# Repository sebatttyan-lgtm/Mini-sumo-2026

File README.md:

# MARK 38(mini sumo)

## DESCRIPCIÓN
El proyecto es un robot mini sumo diseñado por nosotros, con un tamaño y peso correspondiente a las [reglas de la LNR (Liga Nacional de Robótica)](https://sistema.lnr-argentina.com.ar/reglamentos/Sumo). este tiene la capacidad de detectar al contrincante para ir y atacar al otro mini sumo con el que este compitiendo para dejarlo fuera del dojo.

## ADMINISTRADORES DEL PROYECTO
1. **Thiago Lopez.** Diseño 3D y montaje de componentes en placa.
2. **Enzo Zapata.** Diseño de PCB, esquemático y montaje de componentes en placa. 
3. **Sebastián Pérez.** Programación, diseño esquemático y PCB y montaje de componentes en placa. 

## OBJETIVO
Nuestra meta con este proyecto es poder participar en la [LNR(Liga Nacional de Robótica)](https://lnr-argentina.com.ar/) y quedar en un puesto alto a la hora de terminar la competencia.Además, queremos lograr también la programación de mini sumo RC para poder competir entre amigos. 

## ESPECIFICACIONES TÉCNICAS
#### Tamaño del mini sumo: 10cm x 10cm x 8cm
#### Alimentación de operación: 11.1v 450mAh
#### Material empleado en la carrocería: PLA
#### Tipos de sensores empleados: Infrarrojo
#### Fuerza de torque:30Nm (Newton metros)

## COMPONENTES
### - SENSORES DE OBSTÁCULOS
#### [VL53L0X](https://components101.com/sensors/vl53l0x-lidar-distance-sensor) *(x5)*
### - SENSORES DE PISO
#### [QRE1113](https://www.alldatasheet.es/datasheet-pdf/view/54347/FAIRCHILD/QRE1113.html) *(x2)*
### - MOTORES
#### [MICROMOTORES N30 500rpm](https://www.aslongdcmotor.com/photo/aslongdcmotor/document/26865/JGA12-N30.pdf) *(x2)*
### - MICROCONTROLADOR 
#### [ESP32 C3 super mini](www.google.com/search?q=esp32+c3+super+mini&oq=esp32+c3+super+mini&gs_lcrp=EgZjaHJvbWUyBggAEEUYOdIBCDg1NzBqMGo3qAIAsAIA&sourceid=chrome&ie=UTF-8) *(x1)* 
### - DRIVER DE MOTOR (puente H)
#### [TA6586](https://www.alldatasheet.com/datasheet-pdf/pdf/1761575/RZ-MIC/TA6586.html) *(x2)*
### - BATERIA
#### [Tattu 3S 450mAh 11.1V 75C XT30](https://www.hobbymotors.com.ar/store/index.php?route=product/product&product_id=1127) *(x1)*
> (estos componentes son a grandes rasgos y no se han colocado todos los componentes, en el archivo "lista de componentes se encontrarán todos los materiales utilizados durante la produccion").

## DISEÑO DE LA PLACA

<div align="center">

## DISEÑO ESQUEMÁMITCO

<div align="center">

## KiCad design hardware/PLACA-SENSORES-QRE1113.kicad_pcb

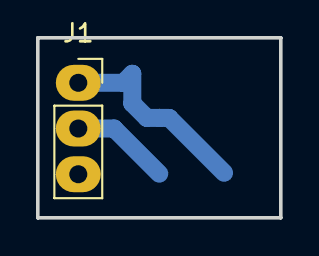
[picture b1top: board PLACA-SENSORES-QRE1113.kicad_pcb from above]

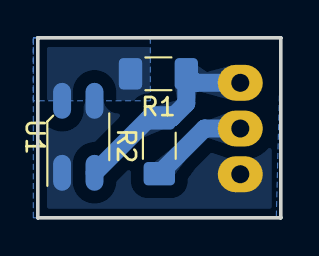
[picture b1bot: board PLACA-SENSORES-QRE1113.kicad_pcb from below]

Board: 2 copper layers, 13.5 x 10.0 mm, 4 parts (3 on the bottom side), 4 nets.

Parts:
J1: Conn_01x03; PinSocket_1x03_P2.54mm_Vertical
R1: 100; R_1206_3216Metric_Pad1.30x1.75mm_HandSolder
R2: 220; R_1206_3216Metric_Pad1.30x1.75mm_HandSolder
U1: QRE1113; OnSemi_CASE100AQ

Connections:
GND: J1.3, U1.2 (K), U1.4
unnamed: J1.2, R2.1
unnamed: R1.2, U1.1 (A)
VCC: J1.1, R1.1, R2.2, U1.3

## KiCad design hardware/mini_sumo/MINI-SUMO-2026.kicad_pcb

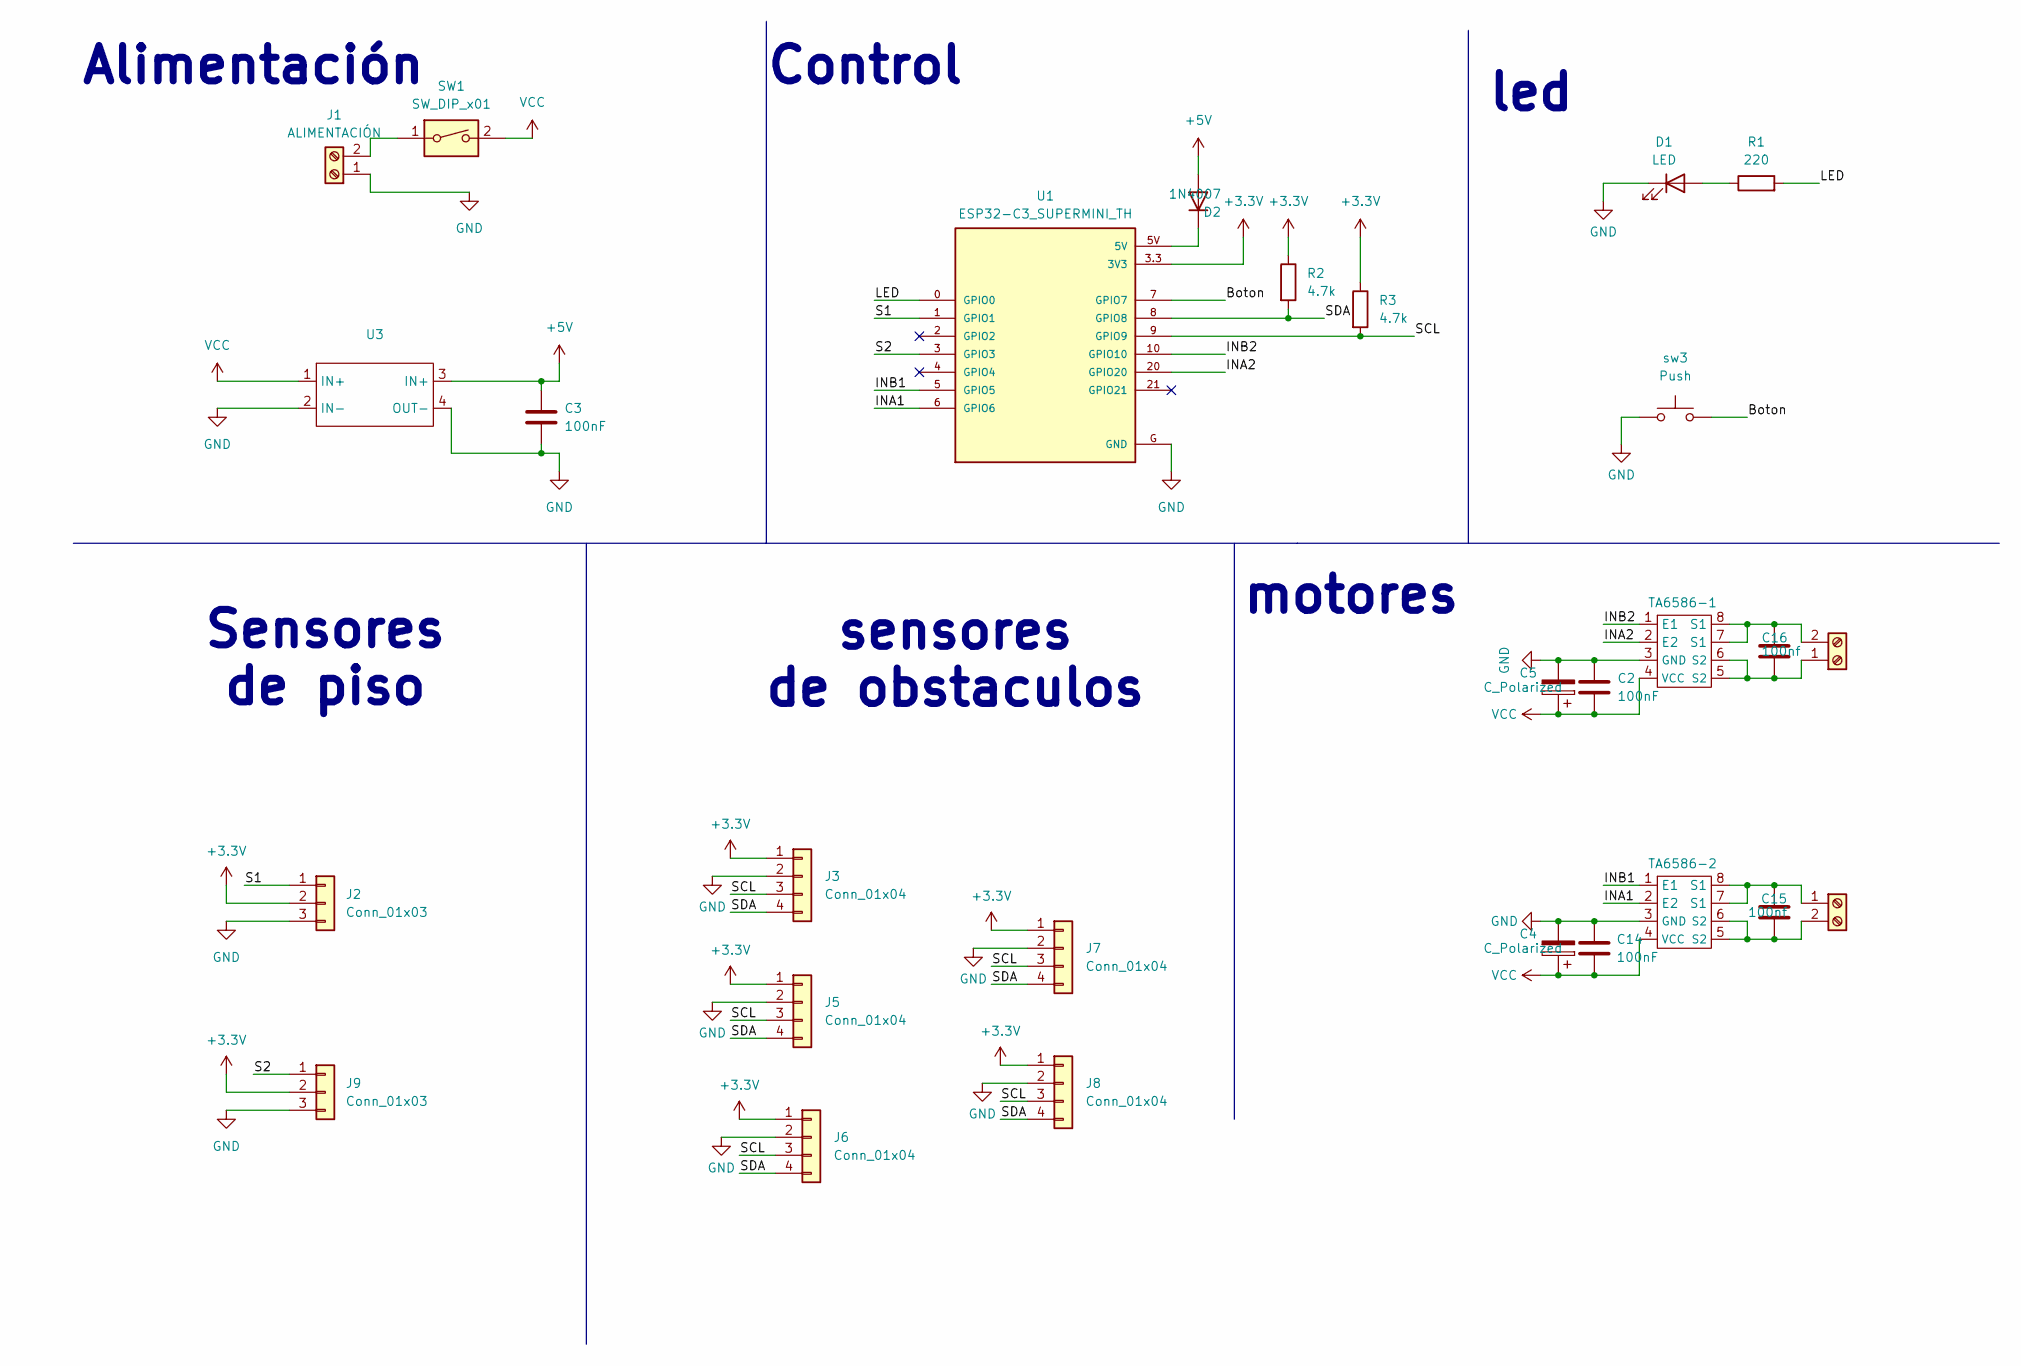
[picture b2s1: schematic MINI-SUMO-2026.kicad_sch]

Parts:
C2, C3, C14: 100nF; C_0805_2012Metric_Pad1.18x1.45mm_HandSolder
C4, C5: C_Polarized; C_Radial_D8.0mm_H11.5mm_P3.50mm
C15, C16: 100nf; C_0805_2012Metric_Pad1.18x1.45mm_HandSolder
D1: LED; PinHeader_1x02_P2.54mm_Vertical
D2: 1N4007; D_SMA_Handsoldering
J1: ALIMENTACIÓN; AMASS_XT30U-F_1x02_P5.0mm_Vertical
J2, J9: Conn_01x03; PinHeader_1x03_P2.54mm_Vertical
J3, J5, J6, J7, J8: Conn_01x04; PinHeader_1x04_P2.54mm_Vertical
M1: M1; JST_XH_S2B-XH-A-1_1x02_P2.50mm_Horizontal
M2: M2; JST_XH_S2B-XH-A-1_1x02_P2.50mm_Horizontal
R1: 220; R_0805_2012Metric_Pad1.20x1.40mm_HandSolder
R2, R3: 4.7k; R_0805_2012Metric_Pad1.20x1.40mm_HandSolder
SW1: SW_DIP_x01; PinHeader_1x02_P2.54mm_Vertical
TA6586-1, TA6586-2: DIP-8_W7.62mm
U1: ESP32-C3_SUPERMINI_TH; MODULE_ESP32-C3_SUPERMINI
U3: Mini360
sw3: Push; SW_PUSH_6mm_H4.3mm

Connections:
+3.3V: J2.2, J3.1, J5.1, J6.1, J7.1, J8.1, J9.2, R2.1, R3.1, U1.3.3 (3V3)
+5V: C3.1, D2.2 (A), U3.3 (IN+)
/Boton: U1.7 (GPIO7), sw3.2
/INA1: TA6586-2.2 (E2), U1.6 (GPIO6)
/INA2: TA6586-1.2 (E2), U1.20 (GPIO20)
/INB1: TA6586-2.1 (E1), U1.5 (GPIO5)
/INB2: TA6586-1.1 (E1), U1.10 (GPIO10)
/LED: R1.2, U1.0 (GPIO0)
/S1: J2.1, U1.1 (GPIO1)
/S2: J9.1, U1.3 (GPIO3)
/SCL: J3.3, J5.3, J6.3, J7.3, J8.3, R3.2, U1.9 (GPIO9)
/SDA: J3.4, J5.4, J6.4, J7.4, J8.4, R2.2, U1.8 (GPIO8)
GND: C2.1, C3.2, C4.2, C5.2, C14.1, D1.1 (K), J1.1, J2.3, J3.2, J5.2, J6.2, J7.2, J8.2, J9.3, TA6586-1.3 (GND), TA6586-2.3 (GND), U1.G (GND), U3.2 (IN-), U3.4 (OUT-), sw3.1
unnamed: D1.2 (A), R1.1
unnamed: D2.1 (K), U1.5V
unnamed: J1.2, SW1.1
unnamed: C16.2, M1.1, TA6586-1.5 (S2), TA6586-1.6 (S2)
unnamed: C16.1, M1.2, TA6586-1.7 (S1), TA6586-1.8 (S1)
unnamed: C15.1, M2.1, TA6586-2.7 (S1), TA6586-2.8 (S1)
unnamed: C15.2, M2.2, TA6586-2.5 (S2), TA6586-2.6 (S2)
VCC: C2.2, C4.1, C5.1, C14.2, SW1.2, TA6586-1.4 (VCC), TA6586-2.4 (VCC), U3.1 (IN+)

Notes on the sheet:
Control
motores
sensores de obstaculos
Sensores de piso
led
Alimentación

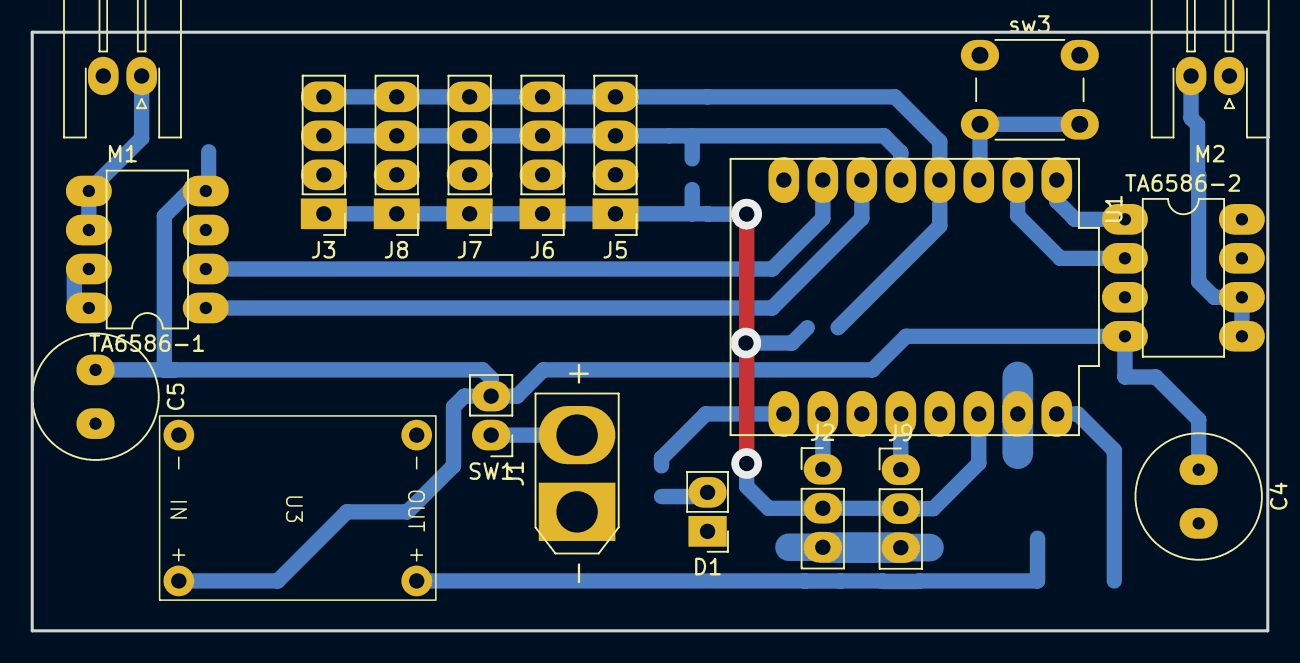
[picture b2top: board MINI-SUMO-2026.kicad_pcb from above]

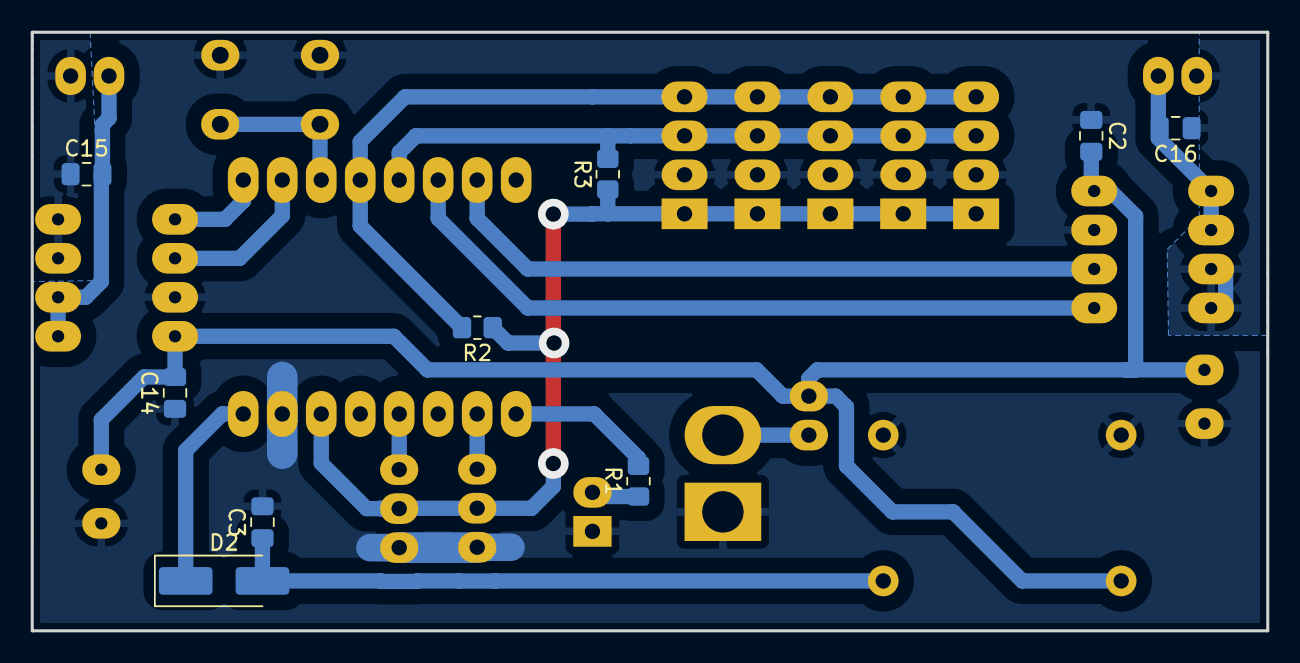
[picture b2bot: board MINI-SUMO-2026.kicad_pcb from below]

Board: 2 copper layers, 80.5 x 39.0 mm, 28 parts (9 on the bottom side), 21 nets.

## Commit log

2026-03-18 primer commit
2026-03-18 modificamos titulo
2026-03-18 Create h
2026-05-12 Create mini_sumo_PCB
2026-05-27 Update README.md
    Primera actualización del readme, aun falta agregar imagenes de pcb, 3d, esquemático
2026-06-03 añadi pcb de sensores en SMD
2026-06-03 Create carpeta-sensores(th)
2026-06-14 Update README.md
    actualización del readme (incluye especificaciones tecnicas y el link de la primera descripción)
2026-06-14 Update eliminar carpeta mal-generada
2026-06-14 Update carpeta-sensores(th)
2026-06-14 Rename PLACA-SENSORES-QRE1113.kicad_pcb to PLACA-SENSORES-QRE1113.kicad_pcb
2026-06-14 Rename PLACA-SENSORES-QRE1113.kicad_prl to PLACA-SENSORES-QRE1113.kicad_prl
2026-06-14 Rename PLACA-SENSORES-QRE1113.kicad_sch to PLACA-SENSORES-QRE1113.kicad_sch
2026-06-14 Rename PLACA-SENSORES-QRE1113.kicad_pro to PLACA-SENSORES-QRE1113.kicad_pro
2026-06-14 Rename fp-info-cache to fp-info-cache
2026-06-14 Rename hardware/PLACA-SENSORES-QRE1113.kicad_pcb to hardware/sensores(SMD)/PLACA-SENSORES-QRE1113.kicad_pcb
2026-06-14 Rename hardware/PLACA-SENSORES-QRE1113.kicad_prl to hardware/sensores(SMD)/PLACA-SENSORES-QRE1113.kicad_prl
2026-06-14 Rename hardware/PLACA-SENSORES-QRE1113.kicad_pro to hardware/sensores(SMD)/PLACA-SENSORES-QRE1113.kicad_pro
2026-06-14 Rename hardware/PLACA-SENSORES-QRE1113.kicad_sch to hardware/sensores(SMD)/PLACA-SENSORES-QRE1113.kicad_sch
2026-06-14 Rename hardware/fp-info-cache to hardware/sensores(SMD)/fp-info-cache
2026-06-14 Create create-docs-directory
2026-06-14 add images to docs
    incluir fotos del pcb, 3d y esquemático del mini sumo y plaqueta de los sensores
2026-06-14 Rename docs/WhatsApp Image 2026-06-14 at 00.52.17 (1).jpeg to MINISUMO-3D-FRONTAL.jpeg
2026-06-14 Rename MINISUMO-3D-FRONTAL.jpeg to docs/MINISUMO-3D-FRONTAL.jpeg
2026-06-14 Rename WhatsApp Image 2026-06-14 at 00.52.17 (2).jpeg to MINISUMO-SCH.jpeg
2026-06-14 Rename WhatsApp Image 2026-06-14 at 00.52.17.jpeg to MINISUMO-PCB.jpeg
2026-06-14 Rename WhatsApp Image 2026-06-14 at 00.59.34.jpeg to SENSORES-PCB.jpeg
2026-06-14 Rename WhatsApp Image 2026-06-14 at 01.03.38.jpeg to SENSORES-SCH.jpeg
2026-06-14 Rename WhatsApp Image 2026-06-14 at 01.04.18.jpeg to SENSORES-3D-FRONTAL.jpeg
2026-06-14 Rename WhatsApp Image 2026-06-14 at 01.04.47.jpeg to SENSORES-3D-TRASERA.jpeg
2026-06-14 Rename WhatsApp Image 2026-06-14 at 01.06.59.jpeg to MINISUMO-3D-TRASERA.jpeg
